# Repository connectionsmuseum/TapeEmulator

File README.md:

Some useful gdb commands:
```
docker run --rm  -it -v `pwd`:/build ctslater/docker-gcc-arm-none-eabi  bash
arm-none-eabi-gdb gcc/TapeEmulator.elf
target extended-remote docker.for.mac.localhost:2331
load
monitor reset
```

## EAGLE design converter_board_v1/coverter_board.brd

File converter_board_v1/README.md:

Pinout
======

JP1 Pin | JP1 Pin | Direction | Function | Adafruit Pin | SAMD Pin |
  ---   |   ---   |    ---    |   ---    |   ------     |   ----   |
   1    |   +5V   |   Power   |          |              |          |
   2    |   +5V   |   Power   |          |              |          |
   3    |   D22   | FROM_CTTC | MANEN0   |   D22        | PD12     |
   4    |   D23   | FROM_CTTC | WRENAB0  |   D23        | PA15     |
   5    |   D24   | FROM_CTTC | WTA10    |   SCL_1      | PC17     |
   6    |   D25   | FROM_CTTC | WTA00    |   SDA_1      | PC16     |
   7    |   D26   | FROM_CTTC | RTA10    |   PCC_DEN1   | PA12     |
   8    |   D27   |           |          |   PCC_DEN2   | PA13     |
   9    |   D28   | FROM_CTTC | RTA00    |   PCC_CLK    | PA14     |
   10   |   D29   |           |          |   PCC_XCLK   | PB19     |
   11   |   +3V3  |   Power   |          |   PCC_D7     | PA23     |
   12   |   D31   |   TO_CTTC | TTBOTA0  |   PCC_D6     | PA22     |
   13   |   D32   |   TO_CTTC | TTEOTA0  |   PCC_D5     | PA21     |
   14   |   D33   |   TO_CTTC | TTRDY0   |   PCC_D4     | PA20     |
   15   |   D34   | FROM_CTTC | WRDATA   |   PCC_D3     | PA19     |
   16   |   D35   |           |          |   PCC_D2     | PB18     |
   17   |   D36   |   TO_CTTC | RDCLK0   |   PCC_D1     | PA17     |
   18   |   D37   |   TO_CTTC | RDDATA0  |   PCC_D0     | PA16     |
   19   |   D38   |           |          |   PCC_D9     | PB15     |
   20   |   D39   |           |          |   PCC_D8     | PB14     |
   21   |   D40   |   TO_CTTC | DATDET0  |   PCC_D11    | PC13     |
   22   |   D41   |   TO_CTTC | TIMA0    |   PCC_D10    | PC12     |
   23   |   D42   |   TO_CTTC | RWDINGA0 |   PCC_D13    | PC15     |
   24   |   D43   |   TO_CTTC | LPEW0    |   PCC_D12    | PC14     |
   25   |   D44   |   TO_CTTC | CARTWE0  |   D44        | PC11     |
   26   |   D45   |   TO_CTTC | TOR0     |   D45        | PC10     |
   27   |   D46   | FROM_CTTC | TTMSPT0  |   D46        | PC06     |
   28   |   D47   | FROM_CTTC | TTREWC0  |   D47        | PC07     |
   29   |   D48   | FROM_CTTC | TTINIT0  |   D48        | PC04     |
   30   |   D49   | FROM_CTTC | TTSEL0   |   D49        | PC05     |
   31   |   D50   | FROM_CTTC | TTSR0    |   MISO       | PD11     |
   32   |   D51   | FROM_CTTC | TTFR0    |   MOSI       | PD08     |
   33   |   D52   | FROM_CTTC | TTSF0    |   SCK        | PD09     |
   34   |   D53   | FROM_CTTC | TTFF0    |   SS         | PD10     |
   35   |   GND   |  Power    |          |              |          |
   36   |   GND   |  Power    |          |              |          |

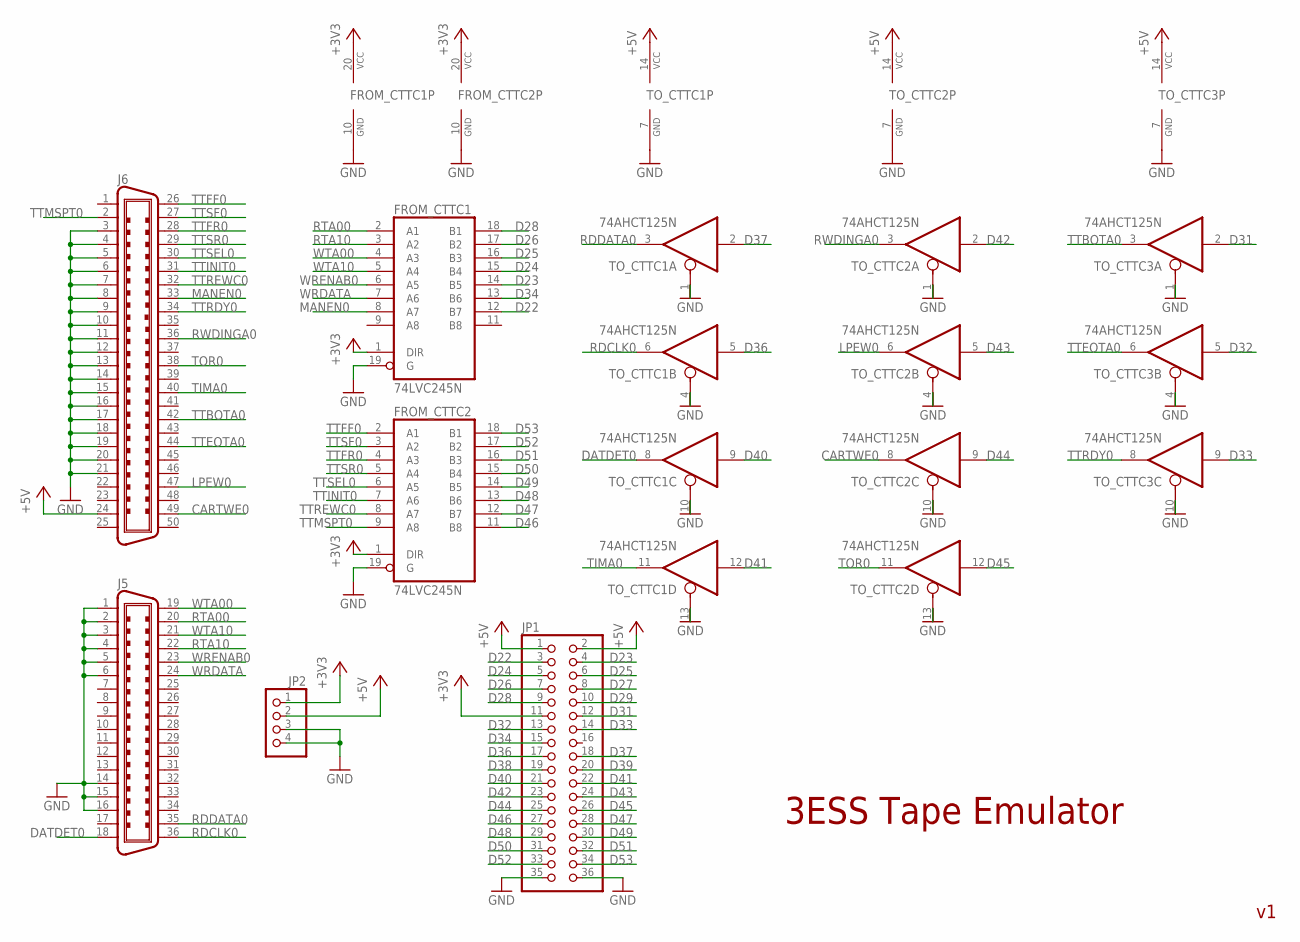
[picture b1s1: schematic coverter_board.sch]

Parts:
FROM_CTTC1, FROM_CTTC2: 74LVC245N; DIL20
J5: C36V; 36V
J6: C50V; 50V
JP1: PINHD-2X18; 2X18
JP2: PINHD-1X4; 1X04
TO_CTTC1, TO_CTTC2, TO_CTTC3: 74AHCT125N; DIL14

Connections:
+3V3: FROM_CTTC1.1 (DIR), FROM_CTTC1.20 (VCC), FROM_CTTC2.1 (DIR), FROM_CTTC2.20 (VCC), JP1.11, JP2.1
+5V: J6.24, JP1.1, JP1.2, JP2.2, TO_CTTC1.14 (VCC), TO_CTTC2.14 (VCC), TO_CTTC3.14 (VCC)
CARTWE0: J6.49, TO_CTTC2.8 (O)
D22: FROM_CTTC1.12 (B7), JP1.3
D23: FROM_CTTC1.14 (B5), JP1.4
D24: FROM_CTTC1.15 (B4), JP1.5
D25: FROM_CTTC1.16 (B3), JP1.6
D26: FROM_CTTC1.17 (B2), JP1.7
D27: JP1.8
D28: FROM_CTTC1.18 (B1), JP1.9
D29: JP1.10
D31: JP1.12, TO_CTTC3.2 (I)
D32: JP1.13, TO_CTTC3.5 (I)
D33: JP1.14, TO_CTTC3.9 (I)
D34: FROM_CTTC1.13 (B6), JP1.15
D36: JP1.17, TO_CTTC1.5 (I)
D37: JP1.18, TO_CTTC1.2 (I)
D38: JP1.19
D39: JP1.20
D40: JP1.21, TO_CTTC1.9 (I)
D41: JP1.22, TO_CTTC1.12 (I)
D42: JP1.23, TO_CTTC2.2 (I)
D43: JP1.24, TO_CTTC2.5 (I)
D44: JP1.25, TO_CTTC2.9 (I)
D45: JP1.26, TO_CTTC2.12 (I)
D46: FROM_CTTC2.11 (B8), JP1.27
D47: FROM_CTTC2.12 (B7), JP1.28
D48: FROM_CTTC2.13 (B6), JP1.29
D49: FROM_CTTC2.14 (B5), JP1.30
D50: FROM_CTTC2.15 (B4), JP1.31
D51: FROM_CTTC2.16 (B3), JP1.32
D52: FROM_CTTC2.17 (B2), JP1.33
D53: FROM_CTTC2.18 (B1), JP1.34
DATDET0: J5.18, TO_CTTC1.8 (O)
GND: FROM_CTTC1.10 (GND), FROM_CTTC1.19 (G), FROM_CTTC2.10 (GND), FROM_CTTC2.19 (G), J5.1, J5.2, J5.3, J5.4, J5.5, J5.6, J5.14, J5.15, J5.16, J6.3, J6.4, J6.5, J6.6, J6.7, J6.8, J6.9, J6.10, J6.11, J6.12, J6.13, J6.14, J6.15, J6.16, J6.17, J6.18, J6.19, J6.20, J6.21, JP1.35, JP1.36, JP2.3, JP2.4, TO_CTTC1.1 (OE), TO_CTTC1.4 (OE), TO_CTTC1.7 (GND), TO_CTTC1.10 (OE), TO_CTTC1.13 (OE), TO_CTTC2.1 (OE), TO_CTTC2.4 (OE), TO_CTTC2.7 (GND), TO_CTTC2.10 (OE), TO_CTTC2.13 (OE), TO_CTTC3.1 (OE), TO_CTTC3.4 (OE), TO_CTTC3.7 (GND), TO_CTTC3.10 (OE)
LPEW0: J6.47, TO_CTTC2.6 (O)
MANEN0: FROM_CTTC1.8 (A7), J6.33
RDCLK0: J5.36, TO_CTTC1.6 (O)
RDDATA0: J5.35, TO_CTTC1.3 (O)
RTA00: FROM_CTTC1.2 (A1), J5.20
RTA10: FROM_CTTC1.3 (A2), J5.22
RWDINGA0: J6.36, TO_CTTC2.3 (O)
TIMA0: J6.40, TO_CTTC1.11 (O)
TOR0: J6.38, TO_CTTC2.11 (O)
TTBOTA0: J6.42, TO_CTTC3.3 (O)
TTEOTA0: J6.44, TO_CTTC3.6 (O)
TTFF0: FROM_CTTC2.2 (A1), J6.26
TTFR0: FROM_CTTC2.4 (A3), J6.28
TTINIT0: FROM_CTTC2.7 (A6), J6.31
TTMSPT0: FROM_CTTC2.9 (A8), J6.2
TTRDY0: J6.34, TO_CTTC3.8 (O)
TTREWC0: FROM_CTTC2.8 (A7), J6.32
TTSEL0: FROM_CTTC2.6 (A5), J6.30
TTSF0: FROM_CTTC2.3 (A2), J6.27
TTSR0: FROM_CTTC2.5 (A4), J6.29
WRDATA: FROM_CTTC1.7 (A6), J5.24
WRENAB0: FROM_CTTC1.6 (A5), J5.23
WTA00: FROM_CTTC1.4 (A3), J5.19
WTA10: FROM_CTTC1.5 (A4), J5.21

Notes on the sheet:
3ESS Tape Emulator

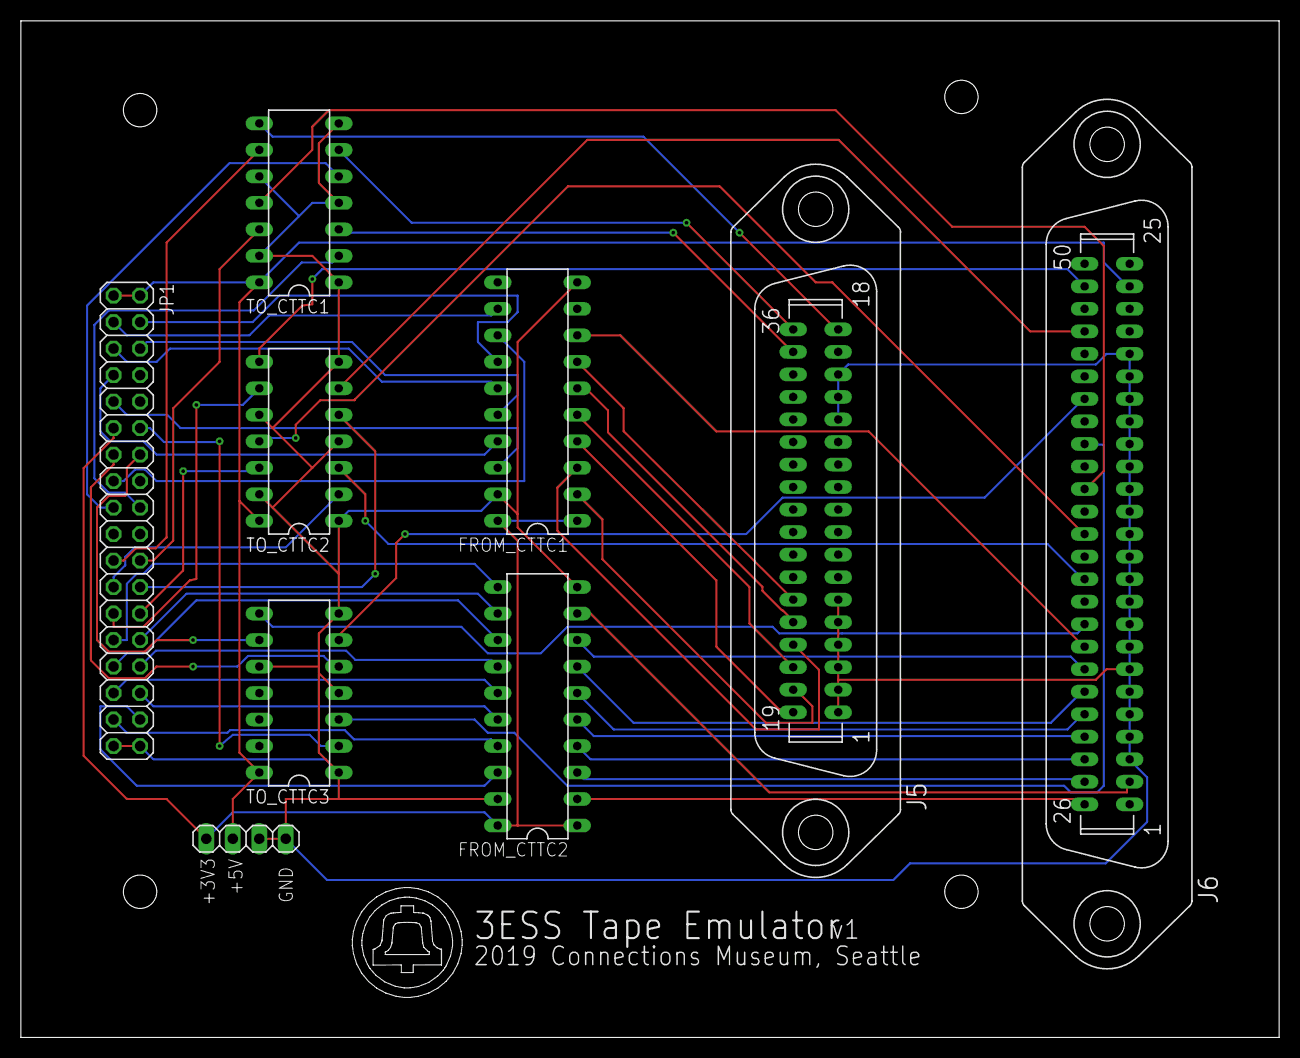
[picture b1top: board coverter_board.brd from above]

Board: 2 copper layers, 120.6 x 97.5 mm, 9 parts (0 on the bottom side), 55 nets.

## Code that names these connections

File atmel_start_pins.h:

/*
 * Code generated from Atmel Start.
 *
 * This file will be overwritten when reconfiguring your Atmel Start project.
 * Please copy examples or other code you want to keep to a separate file
 * to avoid losing it when reconfiguring.
 */
#ifndef ATMEL_START_PINS_H_INCLUDED
#define ATMEL_START_PINS_H_INCLUDED

#include <hal_gpio.h>

// SAMD51 has 14 pin functions

#define GPIO_PIN_FUNCTION_A 0
#define GPIO_PIN_FUNCTION_B 1
#define GPIO_PIN_FUNCTION_C 2
#define GPIO_PIN_FUNCTION_D 3
#define GPIO_PIN_FUNCTION_E 4
#define GPIO_PIN_FUNCTION_F 5
#define GPIO_PIN_FUNCTION_G 6
#define GPIO_PIN_FUNCTION_H 7
#define GPIO_PIN_FUNCTION_I 8
#define GPIO_PIN_FUNCTION_J 9
#define GPIO_PIN_FUNCTION_K 10
#define GPIO_PIN_FUNCTION_L 11
#define GPIO_PIN_FUNCTION_M 12
#define GPIO_PIN_FUNCTION_N 13

#define PA04 GPIO(GPIO_PORTA, 4)
#define PA05 GPIO(GPIO_PORTA, 5)
#define PA06 GPIO(GPIO_PORTA, 6)
#define PA08 GPIO(GPIO_PORTA, 8)
#define PA09 GPIO(GPIO_PORTA, 9)
#define PA10 GPIO(GPIO_PORTA, 10)
#define PA11 GPIO(GPIO_PORTA, 11)
#define PA24 GPIO(GPIO_PORTA, 24)
#define PA25 GPIO(GPIO_PORTA, 25)
#define D12 GPIO(GPIO_PORTB, 0)
#define D13 GPIO(GPIO_PORTB, 1)
#define D9 GPIO(GPIO_PORTB, 2)
#define A2 GPIO(GPIO_PORTB, 3)
#define PB10 GPIO(GPIO_PORTB, 10)
#define PB11 GPIO(GPIO_PORTB, 11)
#define PB15 GPIO(GPIO_PORTB, 15)
#define D10 GPIO(GPIO_PORTB, 22)
#define D11 GPIO(GPIO_PORTB, 23)
#define PCC_D0 GPIO(GPIO_PORTA, 16)

// SD Card detect
#define PB31 GPIO(GPIO_PORTB, 31)

#define NEOPIX GPIO(GPIO_PORTC, 24)

// Deprecated
// #define PIN_FORWARD GPIO(GPIO_PORTC, 11) // D44
// #define PIN_FF      GPIO(GPIO_PORTC, 10) // D45
// #define PIN_REV     GPIO(GPIO_PORTC,  6) // D46
// #define PIN_FR      GPIO(GPIO_PORTC,  4) // D48


// SERCOM ports for data out
// Deprecated
// #define D37 GPIO(GPIO_PORTA, 16) // PCC_D0, SERCOM1.0+3.1
// #define D36 GPIO(GPIO_PORTA, 17) // PCC_D1, SERCOM1.1+3.0
// #define D35 GPIO(GPIO_PORTA, 18) // PCC_D2, SERCOM1.2+3.2
// #define D34 GPIO(GPIO_PORTA, 19) // PCC_D3, SERCOM1.3+3.3

// SD Card SERCOM
#define PB26 GPIO(GPIO_PORTB, 26) // 102, SD_MOSI
#define PB27 GPIO(GPIO_PORTB, 27) // 103, SD_SCK
#define PB29 GPIO(GPIO_PORTB, 29) // 105, SD_MISO
#define SD_CD GPIO(GPIO_PORTB, 31)
#define SD_CS GPIO(GPIO_PORTB, 28)

//
// Connector to the converter board. Using pin names from 3A CC documentation.
//
// Following are FROM_CTTC
#define MANEN0 GPIO(GPIO_PORTD, 12)
#define WRENAB0 GPIO(GPIO_PORTA, 15)
#define WTA10 GPIO(GPIO_PORTC, 17)
#define WTA00 GPIO(GPIO_PORTC, 16)
#define RTA10 GPIO(GPIO_PORTA, 12)
#define RTA00 GPIO(GPIO_PORTA, 14)

// This powers the input buffer chips.
#define BOARD_3V3 GPIO(GPIO_PORTA, 23)

// Following are TO_CTTC
#define TTBOTA0 GPIO(GPIO_PORTA, 22)
#define TTEOTA0 GPIO(GPIO_PORTA, 21)
#define TTRDY0 GPIO(GPIO_PORTA, 20)

// FROM_CTTC
#define WRDATA GPIO(GPIO_PORTA, 19)  // SERCOM1.3+3.3
#define D35 GPIO(GPIO_PORTA, 18)     // SERCOM1.2+3.2

// Following are TO_CTTC
#define RDCLK0 GPIO(GPIO_PORTA, 17)  // SERCOM1.1+3.0
#define RDDATA0 GPIO(GPIO_PORTA, 16) // SERCOM1.0+3.1
#define DATDET0 GPIO(GPIO_PORTC, 13)
#define TIMA0 GPIO(GPIO_PORTC, 12)
#define RWDINGA0 GPIO(GPIO_PORTC, 15)
#define LPEW0 GPIO(GPIO_PORTC, 14)
#define CARTWE0 GPIO(GPIO_PORTC, 11)
#define TOR0 GPIO(GPIO_PORTC, 10)

// Following are FROM_CTTC
#define TTMSPT0 GPIO(GPIO_PORTC, 6)
#define TTREWC0 GPIO(GPIO_PORTC, 7)
#define TTINIT0 GPIO(GPIO_PORTC, 4)
#define TTSEL0 GPIO(GPIO_PORTC, 5)
#define TTSR0 GPIO(GPIO_PORTD, 11)
#define TTFR0 GPIO(GPIO_PORTD, 8)
#define TTSF0 GPIO(GPIO_PORTD, 9)
#define TTFF0 GPIO(GPIO_PORTD, 10)



#endif // ATMEL_START_PINS_H_INCLUDED

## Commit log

2019-08-04 Initial import from atmel start.
2019-08-04 Update clocks.
2019-08-07 Trying to fix some clock bugs. Still not 120MHz.
2019-08-10 Working clock system, blinking D13. Not consistent with atstart xml.
2019-08-17 LED blinking now works via timer.
2019-08-17 Successfully write to the WS2812.
2019-08-18 Blink to show different tape states.
2019-08-19 Start configuring SERCOM1 for data out.
2019-08-19 Update gitignore.
2019-08-19 Pull SPI DMA driver from atmel start.
2019-08-20 Had to update the pixel timings, no idea why.
2019-08-20 Rearrange code, separate LED handling file.
2019-09-12 DMA transfer partially working, but only sends two bytes.
2019-09-12 DMA fixed; writes out full message.
2019-09-21 Checkpoint, added TC-based timer code from ATStart.
2019-09-21 Try to get some timer ticking.
2019-09-21 Timing is working correctly at 1s and 2.5ms, internal OSC32.
2019-09-21 USB status updates are working.
2019-09-27 Put volts on D10.
2019-09-27 Enable SD and add filesystem code.
2019-09-28 Tried to enable SD card, but it's not on the right pins.
2019-09-28 Tried to enable USB mass storage.
2019-09-30 Testing SD card init inside main, move to fatFS later.
2019-09-30 Successfully got through the SD card init routine.
2019-09-30 Successfully read the SD card and output to the usb console.
2019-11-11 First version of the interface board.
2019-11-21 Update pins for converter board v1.
2019-11-23 Fill in the details on tape motion, current block calculations.
2019-11-23 More status leads and logic.
2019-11-24 checkpoint. Not working properly.
2019-11-30 Break out transfer code. Move all work out of interrupt context.
2019-11-30 Remove FreeRTOS from the build.
2019-12-01 Revise the block buffering logic.
2019-12-02 Fix multi-block reads from SD card.
2019-12-07 Fix output bitrate, and byte-swap the input files.
    Switched SERCOM_1 to use GCLK4, and set GCLK4 to run at 12MHz. With the
    SERCOM at 48MHz, the divider doesn't have enough range to get the output
    bitrate down to the 48kHz we need, so slowing down the SERCOM clock
    makes it fit more comfortably.
2019-12-08 Fix some bugs for sequential block reads.
2019-12-08 Speed up SD card access after initialization.
2019-12-08 Set RWDINGA0 as false.
2019-12-15 Handle INIT0 with an interrupt.
2019-12-15 Scope traces from debugging.
2020-01-04 Fix bugs in early warning holes and data detect.
2020-05-16 sketch out a traversable in-memory representation of a tape
2020-05-16 comments and stuff
